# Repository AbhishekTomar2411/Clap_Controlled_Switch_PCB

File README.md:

# 👏 Clap Controlled LED Switch (Sound Activated)

This repository contains the schematic, PCB layout, and Gerber files for a **clap-controlled LED project** designed in **KiCad**. It uses a microphone, BC547 transistors, and an NE555 timer in monostable mode to toggle an LED upon detecting a sharp sound like a clap.

A great beginner-to-intermediate level project for learning:
- Audio signal amplification
- Transistor biasing
- Pulse triggering using NE555
- PCB layout and design fundamentals

---

## 🛠️ Project Overview

This circuit listens for a **clap or tap sound**, amplifies the microphone signal using two NPN transistors, and triggers a **NE555 timer** to turn ON an LED for a few seconds.

### 🔍 Features:
- Microphone-based sound detection
- 2-stage BC547 transistor amplifier
- NE555 timer in monostable configuration
- Adjustable LED ON duration
- Powered by 9V battery
- Clean, compact PCB layout
- Custom silkscreen for readability

---

## ⚡ Circuit Diagram

---

## 🧾 Components Used

| Component      | Value / Part No. | Quantity |
|----------------|------------------|----------|
| Condenser Mic  | —                | 1        |
| Resistor       | 1kΩ              | 1        |
| Resistor       | 4.7kΩ            | 1        |
| Resistor       | 470Ω             | 1        |
| Resistor       | 330Ω             | 1        |
| Resistor       | 47kΩ             | 1        |
| Capacitor      | 100nF (C1, C3)   | 2        |
| Capacitor      | 100µF (C2)       | 1        |
| Transistor     | BC547            | 2        |
| IC             | NE555            | 1        |
| LED            | Red              | 1        |
| Battery Clip   | 9V snap          | 1        |
| PCB            | Custom-made      | 1        |

---

## 📐 PCB Layout

### Top View (Component Side)

### Bottom View (Solder Side)

### Copper trace (traces)

---

## 📂 Files Included

- `Clap_controlled_LED.kicad_sch` – Schematic file
- `Clap_controlled_LED.kicad_pcb` – PCB layout file
- `gerber/` – Folder with Gerber files for fabrication
- `schematic.png` – Screenshot of schematic
- `front.png` – 3D render or top view of the PCB
- `back.png` – 3D render or bottom copper layer
- `README.md` – This file

---

## ✍️ Author

**Abhishek Tomar**  
B.Tech Electrical Engineering Student  
Passionate about Embedded Systems, PCB Design, and Practical Electronics

---

## 📜 License

This project is open-source under the **MIT License**.  
Feel free to use, modify, and improve it.

---

## 🚀 Getting Started

1. Clone or download this repository.
2. Open `.kicad_sch` and `.kicad_pcb` in **KiCad**.
3. Review or modify the circuit.
4. Generate Gerber files if needed.
5. Order PCB or build it on breadboard.
6. Solder components as shown in the front image.
7. Power the circuit with 9V — clap or tap near the mic, and watch the LED glow!

---

## 🙋‍♂️ Support

If you liked this project, **give it a ⭐**, share feedback, or suggest improvements via issues or pull requests!

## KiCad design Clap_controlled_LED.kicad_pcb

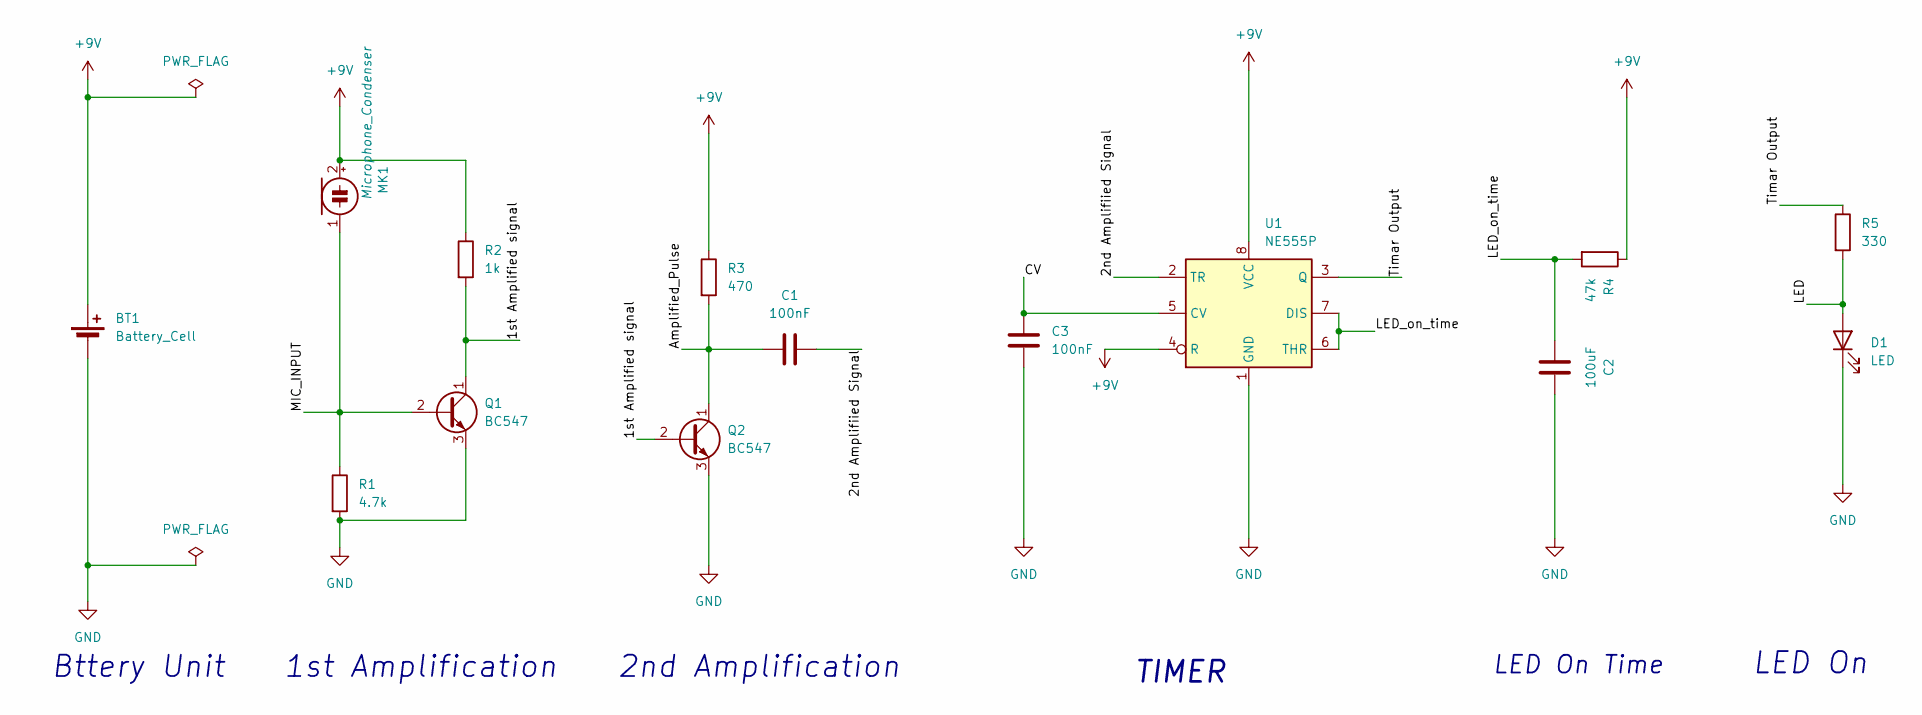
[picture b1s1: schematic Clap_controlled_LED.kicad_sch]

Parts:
BT1: Battery_Cell; BatteryHolder_Eagle_12BH611-GR
C1, C3: 100nF; CP_Radial_D6.3mm_P2.50mm
C2: 100uF; CP_Radial_D6.3mm_P2.50mm
D1: LED; LED_D3.0mm
MK1: Microphone_Condenser; TestPoint_2Pads_Pitch2.54mm_Drill0.8mm
Q1, Q2: BC547; TO-92_Inline
R1: 4.7k; R_Axial_DIN0207_L6.3mm_D2.5mm_P2.54mm_Vertical
R2: 1k; R_Axial_DIN0207_L6.3mm_D2.5mm_P2.54mm_Vertical
R3: 470; R_Axial_DIN0207_L6.3mm_D2.5mm_P2.54mm_Vertical
R4: 47k; R_Axial_DIN0207_L6.3mm_D2.5mm_P2.54mm_Vertical
R5: 330; R_Axial_DIN0207_L6.3mm_D2.5mm_P2.54mm_Vertical
U1: NE555P; DIP-8_W7.62mm

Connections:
+9V: BT1.1 (+), MK1.2 (+), R2.1, R3.1, R4.1, U1.4 (R), U1.8 (VCC)
/1st Amplified signal: Q1.1 (C), Q2.2 (B), R2.2
/2nd Amplifiied Signal: C1.2, U1.2 (TR)
/Amplified_Pulse: C1.1, Q2.1 (C), R3.2
/CV: C3.1, U1.5 (CV)
/LED: D1.2 (A), R5.2
/LED_on_time: C2.1, R4.2, U1.6 (THR), U1.7 (DIS)
/MIC_INPUT: MK1.1 (-), Q1.2 (B), R1.1
/Timar Output: R5.1, U1.3 (Q)
GND: BT1.2 (-), C2.2, C3.2, D1.1 (K), Q1.3 (E), Q2.3 (E), R1.2, U1.1 (GND)

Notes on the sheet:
1st Amplification
2nd Amplification
LED On Time
Bttery Unit
TIMER
LED On

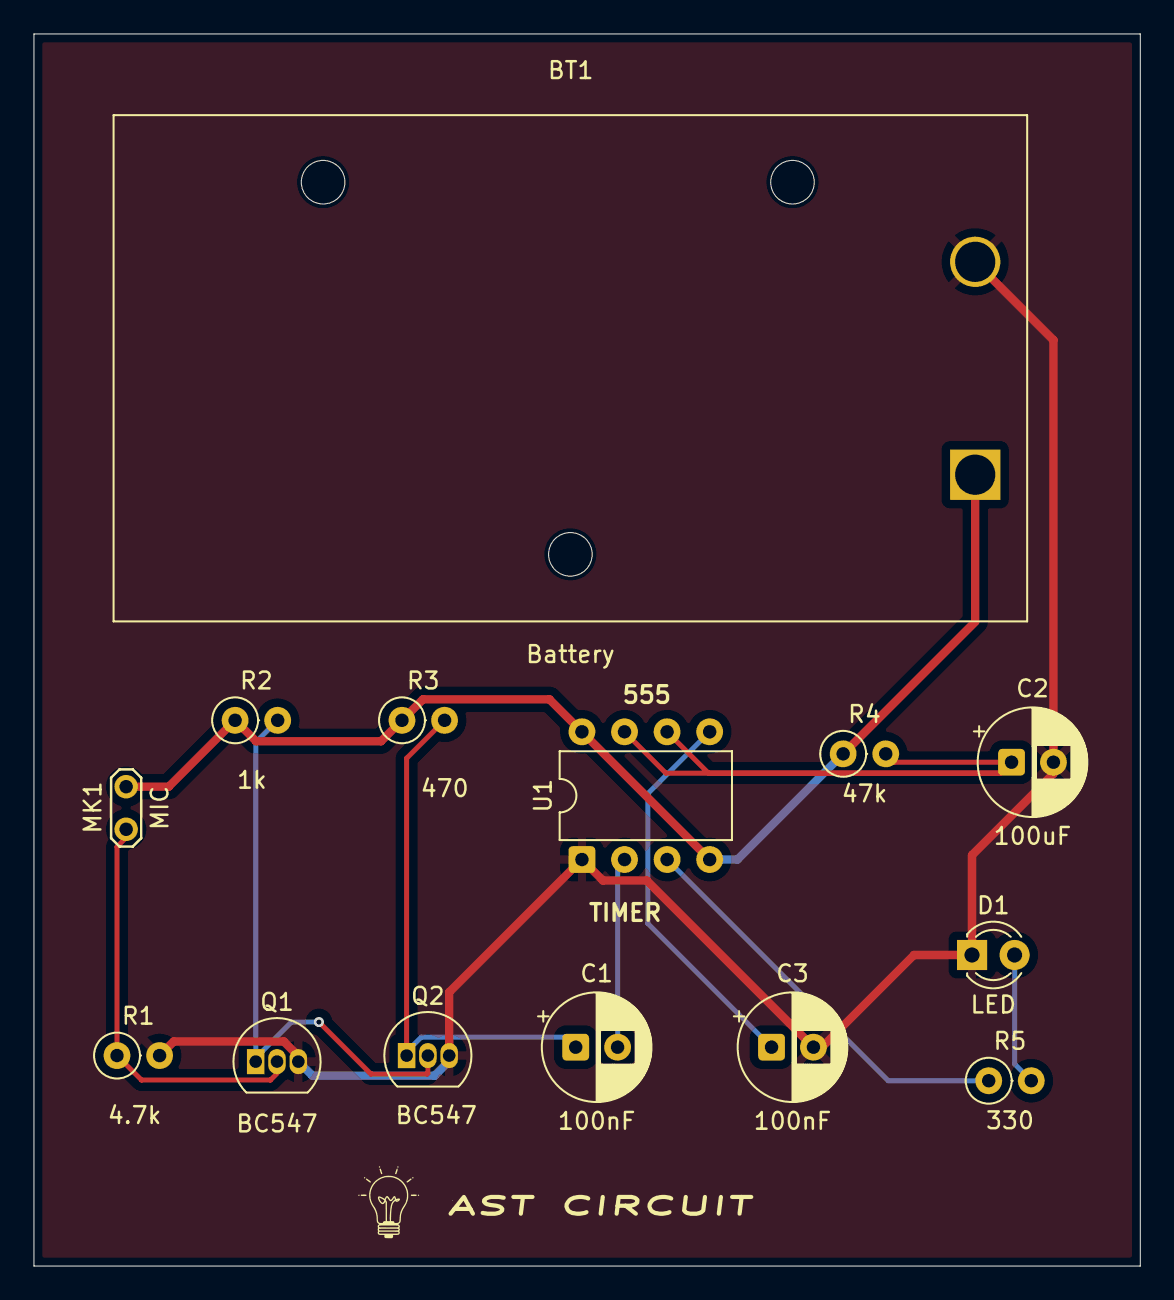
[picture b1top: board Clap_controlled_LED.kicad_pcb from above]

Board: 2 copper layers, 66.0 x 73.5 mm, 14 parts (0 on the bottom side), 10 nets.

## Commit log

2025-07-03 Create pcb
2025-07-03 Initial commit – Clap controlled LED circuit and PCB files
2025-07-03 Create Doc
